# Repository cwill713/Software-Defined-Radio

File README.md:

# Software-Defined-Radio-Reciever
This project, assigned to us by [Dr. Frohne](https://github.com/frohro), combines our professors' interest HAM radio and a practical application of gain, opamp analysis, noise, and AC/DC analysis that we learned in Electronics I. This is the design of Software Defined Radio built in collaboration with [Joshua Mularczyk](https://github.com/JoshuaMularczyk) for our Engineering Electronics II class.

## Design Specifications
When perfroming research for this project, Joshua and I began to figure out what specifations our SDR would follow. Origianlly, we wanted to build a commercial FM radio, but after discusstion with Dr. Frohne, we reconsidered. The final specifications we decided on are as follows:
- Frequency Range: 7MHZ - 18MHz
- Radio Type: Shortwave
- Inexpensive
- Low Noise Figure
- -107 dBm (1uV) Minimum Discernable Signal
- Good Image Rejection

The subcirucits used to create this SDR are: 
- Butterworth Bandpass Filter
- Tayloe Mixer
- Bessel Lowpass Filter
- Power Supply Noise Filter
- 2.5V Voltage Bias
- Arduino Controlled Oscillator

## Theory

This block diagram shows an overveir of how a Software Defined Radio works. A signal is recieved from the antenna and then passes through the band pass filter. Here all desired frequencies are let through and the others discarded. Then the signals are passed through the Tayloe Mmixer where the signal is then split into four new ones that are 90 degrees out of phase. The these signals, the sets that are 180 degrees apart, are combined in a set of opamps that double as lowpass filters to ensure the output signal has a frequency no greater than 100kHz. These new two signals are then passed through the sound card to the system running the [Quisk](https://james.ahlstrom.name/quisk/) software which allows us to hear what is being transmitted on the signal and change the signal taht we are listening to. The Arduino Nano and the Si5351 that runs a [program](https://github.com/cwill713/Software-Defined-Radio/tree/main/Arduino%20Code/New_Quisk_Nano) that allows it to act as our oscillator that can be changed by what ever frequency Quisk is trying to demodulate.

## Schematics
The following are the initial schematics that Joshua and I have designed for the SDR.

### BandPass Filter

We built this bandpass filter using the [LC Filter Design Tool](https://rf-tools.com/lc-filter/). This is a Butterworth Filter that will only allow frequencies between 8MHz and 18MHz to pass through it.

The voltage divider will take our Filtered 5V and output a 2.5 DC voltage to drive the rest of the circuit. 

### Mixer and Lowpass Filter

The mixer that Joshua and I decided to use was  Tayloe Mixer. The Tayloe mixer uses switches to combined the signals that are 180 degrees out of phase with differential amplifiers so that signals above and below the oscilator frequecy can be detected.

The lowpass filter will block all frequencies greater that 100kHz.

### Voltage Smoother

The Voltage Smoother with take the 5V Vcc and remove as much noise as possible that comes in from the computer and outputs a smoother 5V for the SDR to use.

### Arduino and Si5351

The Si5351 programmable oscillator will allow us to input two clock signals that are 90 degrees out of phase into S0 and S1 of the SN74CBT3253. The Arduino Nano will control the frequency the is put out by the Si5351 for tuning.

## Simulations
The following are the simulations of our filters and our SDR as a whole.

### Bandpass Filter

As seen above, the bandpass fitler we designed, as a start band of 7MHz and a stop band of 18MHz.

### Lowpass Filter

After the the I and Q signals from the 2N74CBT3253 are combined in the LT6231 opamps we can see that no frequencies above 100kHz are allowed through.

### Complete SDR

We simulated our complete SDR the combined bandpass simulation, our tayloe mixer, simulated by using four voltage controlled switches the produced 4 pusles that are 90 degrees out of phase, and our lowpass filter simulation. You can see the two outputs are the baseband I and Q output signals that are 90 degrees out of phase.

## Rev 5 PCB Design and Testing
My partner and I each designed our own version of our board, but my partner had the better board layout. So we used his [V5](https://github.com/cwill713/Software-Defined-Radio/tree/main/Schematic%20Files/SDRrecV5) of our schematic, PCB, and drill files and sent them to our professor who sent our files to [JLPCB](https://jlcpcb.com/VGS?utm_source=gg_vgs&utm_medium=cpc&gclid=Cj0KCQjwqPGUBhDwARIsANNwjV4Y9aU908uwwHsgXCAJ3L9PZ44l-hPgCvsU4kgto-ll1H0iRJroh1UaAsKwEALw_wcB) for printing. We then ordered that parts needed then constructed and tested our board. 

Our V5 Circuit Board PCB

### Initial Testing
During the initial testing, a fellow student, [Nicholas Zimmerman](https://github.com/nickz12345), found that we had a wiring issue in our mixer. To fix this issue on my board, I cut the traces on my board and corrected the mistakes with jumper wires. Jumping one of these traces, I made a mistake and broked one of the capacitors, its pad, and the trace to one of the test points. Due to the lack of time to complete the project, Josh and I used his board for our final testing.

We also found that our boards were missing our ground plan, due to it being temporarily turned off when the gerber files were generated. To fix this I manually wired all the grounds to the ground on the BNC connector.

The last mistake we had was in the second lowpass filter. When had the the second set of opamps running between Vcc and ground instead of Vcc and -Vcc. Because of this, this set of opamps had enough gain that they became saturated. Luckily for us, this second lowpass filter was a back up for the first. We decided to bypass the second lowpass filter because the output signal from the first lowpass filter was exactly what we needed.

The images of our boards can be seen [here](https://github.com/cwill713/Software-Defined-Radio/tree/main/Pictures).

### V6 PCB Design

After fixing these mistakes on the board, I fixed these issues in the [V6](https://github.com/cwill713/Software-Defined-Radio/tree/main/Schematic%20Files/SDRrecV6) KiCAD files.

## Project Resuslts
### Minimum Discenable Signal
When testing to see the minimum discernible signal we connected our board up to our signal generator, our system running quisk software, and our soundcard. We adjusted the attenuator on the signal generator to output a signal of 14.19MHz and adjusted the attenuator to see how small of a signal we could detect. In the image below, we see our radio discern a signal of .35uV!

### Practical Test
Next, we decided to see if we could find any bandwidths where people were talking and try to listen in. To do this, we disconnected the board from the signal generator and connected our board to the antenna of our building. Scanning the differnt frequencies we found two bandwidths being used for communications.

The first was being used to communicate the weather from what we are assuming to be an air traffic control tower. 

"Wind 360 degrees, light drizzle, visibility more than 6 miles".

The second bandwidth was being used as an automated message that repeated the time once a minute.

"At the tone ***** _5 hours 52 minutes coordinated universal time"

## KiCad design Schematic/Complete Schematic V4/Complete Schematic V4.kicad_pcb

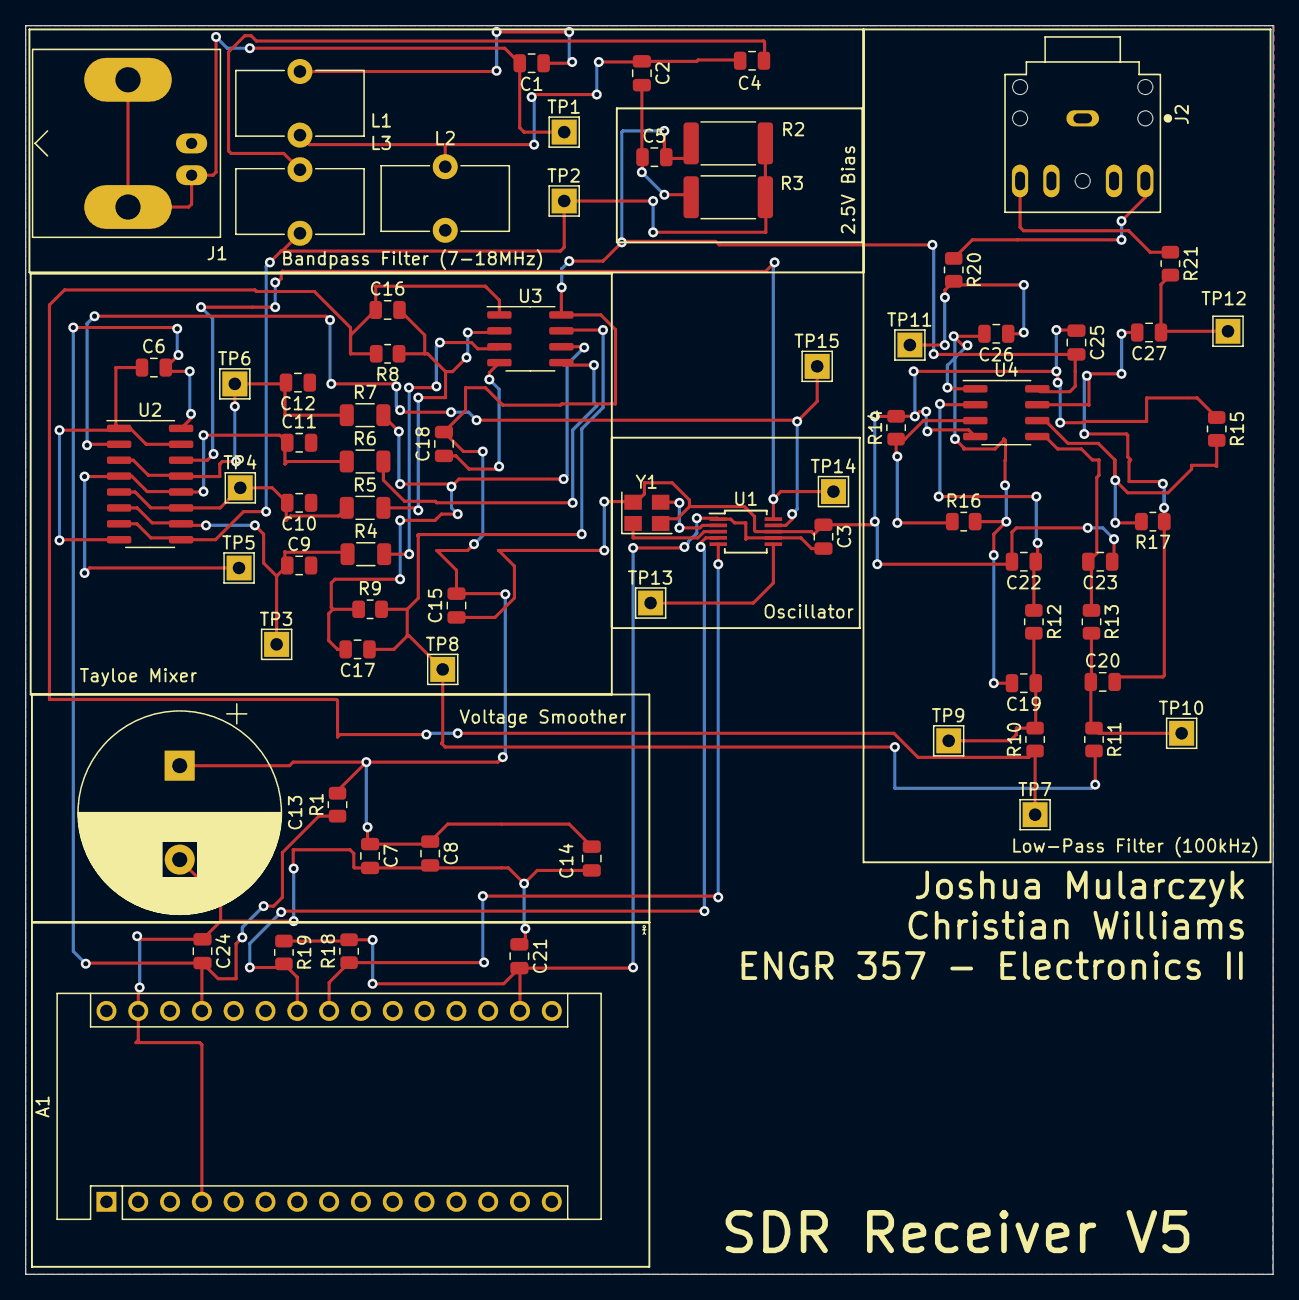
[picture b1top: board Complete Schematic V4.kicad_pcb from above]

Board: 2 copper layers, 99.6 x 99.7 mm, 74 parts (0 on the bottom side), 38 nets.

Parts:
A1: Arduino_Nano_v3.x; Arduino_Nano
C1, C4: 270p; C_0805_2012Metric
C2: 560p; C_0805_2012Metric
C3, C5, C6, C14, C15, C18, C21, C24, C25: 0.1u; C_0805_2012Metric
C7: 10n; C_0805_2012Metric
C8: 100n; C_0805_2012Metric
C9, C10, C11, C12: 5n; C_0805_2012Metric
C13: 8200u; CP_Radial_D16.0mm_P7.50mm
C16, C17: 75p; C_0805_2012Metric
C19, C20, C22, C23: 100p; C_0805_2012Metric
C26, C27: 10u; C_0805_2012Metric
J1: Conn_Coaxial; BNC_Amphenol_B6252HB-NPP3G-50_Horizontal
J2: SJ1-3525N; CUI_SJ1-3525N
L1, L3: 750n; L_Toroid_Vertical_L10.0mm_W5.0mm_P5.08mm
L2: 360n; L_Toroid_Vertical_L10.0mm_W5.0mm_P5.08mm
R1: 1; R_0805_2012Metric
R2, R3: 10k; R_2512_6332Metric
R4, R5, R6, R7: 200; R_1206_3216Metric
R8, R9: 22k; R_0805_2012Metric
R10, R11: 4.64k; R_0805_2012Metric
R12, R13: 52.3k; R_0805_2012Metric
R14, R15: 2.49k; R_0805_2012Metric
R16, R17: 17.4k; R_0805_2012Metric
R18, R19: 4.7k; R_0805_2012Metric
R20, R21: 100; R_0805_2012Metric
TP1, TP2, TP3, TP4, TP5, TP6, TP7, TP8, TP9, TP10, TP11, TP12, TP13, TP14, TP15: TestPoint; TestPoint_THTPad_2.0x2.0mm_Drill1.0mm
U1: Si5351A-B-GT; MSOP-10_3x3mm_P0.5mm
U2: SN74CBT3253; SOIC-16_3.9x9.9mm_P1.27mm
U3: LT6231; SOIC-8_3.9x4.9mm_P1.27mm
U4: LM4562MA; SOIC-8_3.9x4.9mm_P1.27mm
Y1: Crystal_GND24_Small; Crystal_SMD_3225-4Pin_3.2x2.5mm

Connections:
+3V3: A1.17 (3V3), C3.2, C21.2, R18.2, R19.1, U1.1 (VDD), U1.7 (VDDO)
+5V: A1.27 (+5V), C6.2, C24.2, R1.1, U2.16 (VCC)
/SCL: A1.24 (A5), R19.2, U1.4 (SCL)
/SDA: A1.23 (A4), R18.1, U1.5 (SDA)
Filtered 5V: C5.2, C7.1, C8.1, C13.1, C14.2, C15.2, C18.2, C25.2, R1.2, R2.1, U3.8 (V+), U4.8 (V+)
GND: A1.4 (GND), A1.29 (GND), C2.2, C3.1, C5.1, C6.1, C7.2, C8.2, C9.2, C10.1, C11.2, C12.1, C13.2, C14.1, C15.1, C18.1, C21.1, C22.2, C23.1, C24.1, C25.1, J1.1 (In), J2.1, L2.2, R3.2, R14.2, R15.1, U1.8 (GND), U2.1 (1~OE), U2.8 (GND), U2.15 (2~OE), U3.4 (V-), U4.4 (V-), Y1.2, Y1.4
unnamed: C1.1, L1.1
unnamed: C1.2, J1.2 (Ext), TP1.1
unnamed: C2.1, C4.1, L1.2, L2.1
unnamed: C4.2, L3.1
unnamed: C9.1, R4.1, TP3.1, U2.6 (1B1), U2.10 (2B1)
unnamed: C10.2, R5.1, TP4.1, U2.5 (1B2), U2.11 (2B2)
unnamed: C11.1, R6.1, TP5.1, U2.4 (1B3), U2.12 (2B3)
unnamed: C12.2, R7.1, TP6.1, U2.3 (1B4), U2.13 (2B4)
unnamed: C16.1, R8.2, R10.1, TP7.1, U3.1
unnamed: C16.2, R5.2, R8.1, U3.2 (-)
unnamed: C17.1, R9.2, R11.2, TP8.1, U3.7
unnamed: C17.2, R7.2, R9.1, U3.6 (-)
unnamed: C19.1, R10.2, R12.2, TP9.1
unnamed: C19.2, C26.2, R16.2, U4.1
unnamed: C20.1, R11.1, R13.2, TP10.1
unnamed: C20.2, C27.2, R17.1, U4.7
unnamed: C22.1, R12.1, U4.2 (-)
unnamed: C23.2, R13.1, U4.5 (+)
unnamed: C26.1, R20.2, TP11.1
unnamed: C27.1, R21.2, TP12.1
unnamed: J2.2, R21.1
unnamed: J2.3, R20.1
unnamed: L3.2, R2.2, R3.1, TP2.1, U2.7 (1A), U2.9 (2A)
unnamed: R4.2, U3.3 (+)
unnamed: R6.2, U3.5 (+)
unnamed: R14.1, R16.1, U4.3 (+)
unnamed: R15.2, R17.2, U4.6 (-)
unnamed: TP13.1, U1.6 (CLK2)
unnamed: TP14.1, U1.10 (CLK0), U2.14 (S0)
unnamed: TP15.1, U1.9 (CLK1), U2.2 (S1)
unnamed: U1.2 (XA), Y1.3
unnamed: U1.3 (XB), Y1.1

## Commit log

2022-04-18 Create Simulation Holder
2022-04-18 Lowpass and Bandpass Filters
2022-04-18 Create Schematics
2022-04-18 Create holder
2022-04-18 Schematics v1
2022-04-19 Complete Schematic v3
2022-04-19 Added bypass capacitors to our schematic
2022-04-21 Added pull up resistors, bypass capacitors, split the gain between our amplifiers, and changes our bypass filter to 7-18 Mhz
2022-04-25 New Complete Schematic Versions
2022-04-28 New Update
2022-04-28 Schematic with all footprints for checking and the parts lists with the links
2022-04-28 updated schematic
2022-04-28 auto saves
2022-04-28 PCB Design
2022-04-29 Final Schematic and PCB
2022-05-01 Final Changes before PCB sent out
2022-05-02 Christian's PCB Work, But Josh's PCB Design is what we're using
2022-05-02 no message
2022-05-02 trying to update christian v3
2022-06-01 updated values
2022-06-02 new changes to orgnization
2022-06-02 offical changes is files we need
2022-06-02 Organization Changes. Deleted files we don't use, and organized the rest into properly names files.
2022-06-03 Created New Folders
2022-06-03 Renamed Versions of our schematics
2022-06-06 Updated V6 Board
2022-06-06 Addel Gerber, PDF, and Drill Files. Addes Pictures Folder
2022-06-08 Merge branch 'main' of https://github.com/cwill713/Software-Defined-Radio into Christian_V4
    # Conflicts:
    # Schematic Files/Complete Schematic V4/Complete Schematic V4-backups/Complete Schematic V4-2022-04-28_000705.zip
    # Schematic Files/Complete Schematic V4/Complete Schematic V4-backups/Complete Schematic V4-2022-04-28_035923.zip
    # Schematic Files/Complete Schematic V4/Complete Schematic V4-backups/Complete Schematic V4-2022-04-28_040923.zip
    # Schematic Files/Complete Schematic V4/Complete Schematic V4-backups/Complete Schematic V4-2022-04-28_041923.zip
    # Schematic Files/Complete Schematic V4/Complete Schematic V4-backups/Complete Schematic V4-2022-04-28_042923.zip
